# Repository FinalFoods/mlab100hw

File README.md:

# mlab100hw
Hardware Microbiota Personal Lab 100

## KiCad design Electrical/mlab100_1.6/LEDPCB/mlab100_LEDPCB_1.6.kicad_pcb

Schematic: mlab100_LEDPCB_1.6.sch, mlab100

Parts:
J14, J15, J16: Conn_01x06_Male; Pin_Header_Angled_2x03_Pitch1.27mm

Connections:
/LEDBoard1/3V3: J14.5; also elsewhere on the board
/LEDBoard1/12V: J14.6; also elsewhere on the board
/LEDBoard1/GND: J14.1, J14.2; also elsewhere on the board
/LEDBoard1/LED: J14.4; also elsewhere on the board
/LEDBoard1/Temp1w: J14.3; also elsewhere on the board
/LEDBoard2/3V3: J15.5; also elsewhere on the board
/LEDBoard2/12V: J15.6; also elsewhere on the board
/LEDBoard2/GND: J15.1, J15.2; also elsewhere on the board
/LEDBoard2/LED: J15.4; also elsewhere on the board
/LEDBoard2/Temp1w: J15.3; also elsewhere on the board
/LEDBoard3/3V3: J16.5; also elsewhere on the board
/LEDBoard3/12V: J16.6; also elsewhere on the board
/LEDBoard3/GND: J16.1, J16.2; also elsewhere on the board
/LEDBoard3/LED: J16.4; also elsewhere on the board
/LEDBoard3/Temp1w: J16.3; also elsewhere on the board

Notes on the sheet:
LED_Temp_Panel

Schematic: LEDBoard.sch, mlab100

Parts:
D1, D2, D4: 470nm; LED_D5.0mm
D3, D6, D7: 470nm; LED_0603
R1: 120; R_1210_HandSoldering
R4: 10k; R_0603
R5: 1k3; R_0603
R6: 8k8; R_0603
U4: DS18B20; TO-92_Molded_Narrow

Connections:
/LEDBoard1/3V3: D6.2, U4.3 (VDD); also elsewhere on the board
/LEDBoard1/12V: D1.2, D3.2, D7.2; also elsewhere on the board
/LEDBoard1/GND: R4.2, R5.2, U4.1 (GND); also elsewhere on the board
/LEDBoard1/LED: R1.2, R6.2; also elsewhere on the board
/LEDBoard1/Temp1w: U4.2 (DQ); also elsewhere on the board
unnamed: D1.1, D2.2
unnamed: D2.1, D4.2
unnamed: D3.1, R4.1
unnamed: D4.1, R1.1
unnamed: D6.1, R5.1
unnamed: D7.1, R6.1

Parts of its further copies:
D5, D8, D9, D10, D11, D12: 470nm; LED_D5.0mm
D13, D14, D15, D16, D17, D18: 470nm; LED_0603
R2, R3: 120; R_1210_HandSoldering
R7, R10: 10k; R_0603
R8, R11: 1k3; R_0603
R9, R12: 8k8; R_0603
U5, U6: DS18B20; TO-92_Molded_Narrow

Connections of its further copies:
/LEDBoard2/3V3: D14.2, U5.3 (VDD); also elsewhere on the board
/LEDBoard2/12V: D5.2, D13.2, D15.2; also elsewhere on the board
/LEDBoard2/GND: R7.2, R8.2, U5.1 (GND); also elsewhere on the board
/LEDBoard2/LED: R2.2, R9.2; also elsewhere on the board
/LEDBoard2/Temp1w: U5.2 (DQ); also elsewhere on the board
/LEDBoard3/3V3: D17.2, U6.3 (VDD); also elsewhere on the board
/LEDBoard3/12V: D10.2, D16.2, D18.2; also elsewhere on the board
/LEDBoard3/GND: R10.2, R11.2, U6.1 (GND); also elsewhere on the board
/LEDBoard3/LED: R3.2, R12.2; also elsewhere on the board
/LEDBoard3/Temp1w: U6.2 (DQ); also elsewhere on the board
unnamed: D5.1, D8.2
unnamed: D8.1, D9.2
unnamed: D9.1, R2.1
unnamed: D10.1, D11.2
unnamed: D11.1, D12.2
unnamed: D12.1, R3.1
unnamed: D13.1, R7.1
unnamed: D14.1, R8.1
unnamed: D15.1, R9.1
unnamed: D16.1, R10.1
unnamed: D17.1, R11.1
unnamed: D18.1, R12.1

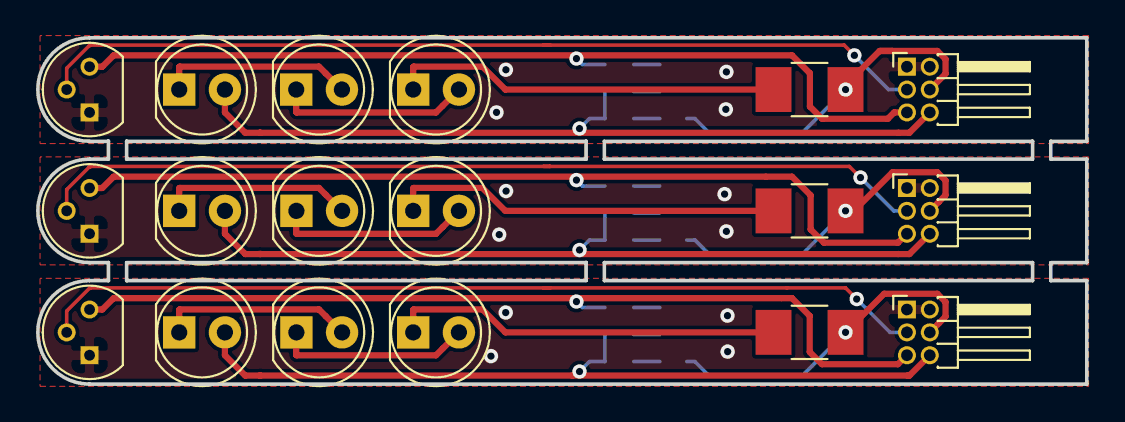
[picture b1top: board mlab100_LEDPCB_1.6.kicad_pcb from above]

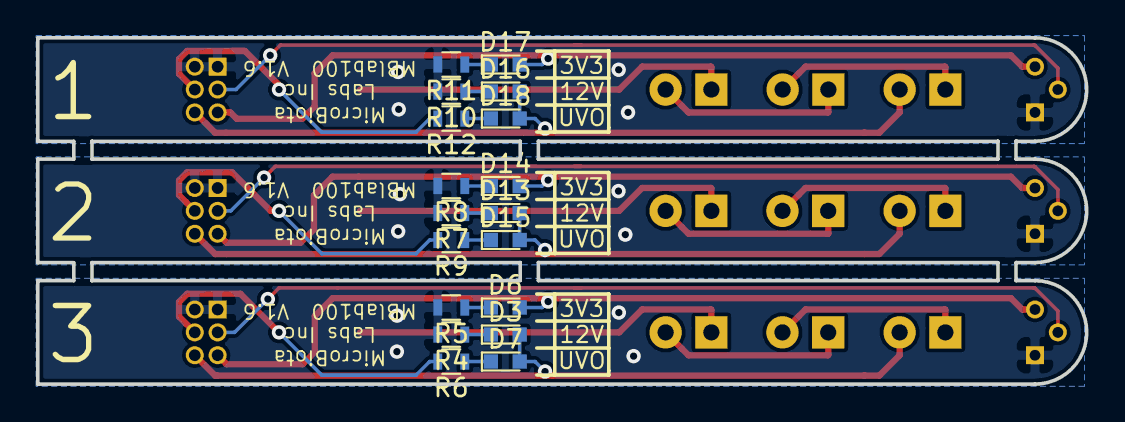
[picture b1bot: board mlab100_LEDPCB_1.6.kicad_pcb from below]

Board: 2 copper layers, 58.3 x 19.2 mm, 36 parts (18 on the bottom side), 33 nets.

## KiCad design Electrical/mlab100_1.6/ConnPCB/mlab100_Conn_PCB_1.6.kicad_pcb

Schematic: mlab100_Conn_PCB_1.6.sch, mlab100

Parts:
J3: Conn_01x12_Male; Pin_Header_Straight_2x06_Pitch2.54mm_SMD
J8, J9, J10: Conn_01x06_Male; Pin_Header_Straight_2x03_Pitch1.27mm
J11, J12, J13: Conn_01x02_Male; Pin_Header_Straight_1x02_Pitch2.54mm
MH8, MH9, MH10: MountingHole; MountingHole_3.7mm_Pad

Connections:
3V3_O: J3.3, J8.2, J9.2, J10.2; also elsewhere on the board
12V_O: J3.1, J8.1, J9.1, J10.1, J11.2, J12.2, J13.2; also elsewhere on the board
/AnalogConnPCB/3V3ACtrl: J3.5; also elsewhere on the board
/AnalogConnPCB/5V: J3.11; also elsewhere on the board
/AnalogConnPCB/470nmCtrl: J3.2; also elsewhere on the board
/AnalogConnPCB/HeaterCtrl: J3.12; also elsewhere on the board
/AnalogConnPCB/SPI_CS_ADC: J3.9; also elsewhere on the board
/AnalogConnPCB/SPI_MISO: J3.8; also elsewhere on the board
/AnalogConnPCB/SPI_MOSI: J3.7; also elsewhere on the board
/AnalogConnPCB/SPI_SCL: J3.6; also elsewhere on the board
GND_O: J3.10, J8.5, J8.6, J9.5, J9.6, J10.5, J10.6; also elsewhere on the board
Heater-: J11.1, J12.1, J13.1; also elsewhere on the board
LED470nm: J8.3, J9.3, J10.3; also elsewhere on the board
Temp1wDaisy: J3.4, J8.4, J9.4, J10.4; also elsewhere on the board

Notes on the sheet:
Conn_Panel

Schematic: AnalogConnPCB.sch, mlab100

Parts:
C1, C2: 1uF; C_0603
C5: 0.1uF; C_0603
D1, D2, D3, D4: LED; LED_0603
D13, D14: D_Photo; LED_D5.0mm
IC1, IC2: ZXGD3006E6QTA; SOT-23-6; Manufacturer_Part_Number ZXGD3006E6QTA; Mouser Part Number 621-ZXGD3006E6QTA
IC3: TCR2EF33,LM(CT; SOT-25; Manufacturer_Part_Number TCR2EF33,LM(CT; DigiKey Part Number TCR2EF33LM(CTDKR-ND
IC4: ADC122S021CIMM_NOPB; SOP65P490X110-8N; Manufacturer_Part_Number ADC122S021CIMM/NOPB
JP1: Jumper; R_0603
Q1, Q3: AOD4184A; TO-252-2
R1, R4: 1k3; R_0603
R2: 3k; R_0603
R3, R15, R16: 10k; R_0603
R12, R13: 3k3; R_0603
R14: 4k7; R_0603

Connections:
3V3_O: D2.2, R14.2; also elsewhere on the board
12V_O: D4.2, IC1.1, IC2.1; also elsewhere on the board
+3.3VA: C2.1, C5.1, D1.2, IC3.5, IC4.2; also elsewhere on the board
/AnalogConnPCB/3V3ACtrl: IC3.3; also elsewhere on the board
/AnalogConnPCB/5V: C1.1, D3.2, IC3.1; also elsewhere on the board
/AnalogConnPCB/470nmCtrl: R13.1; also elsewhere on the board
/AnalogConnPCB/HeaterCtrl: R12.1; also elsewhere on the board
/AnalogConnPCB/SPI_CS_ADC: IC4.1; also elsewhere on the board
/AnalogConnPCB/SPI_MISO: IC4.7; also elsewhere on the board
/AnalogConnPCB/SPI_MOSI: IC4.6; also elsewhere on the board
/AnalogConnPCB/SPI_SCL: IC4.8; also elsewhere on the board
/AnalogConnPCB/sheet5C67EBE6/A+: D13.1; also elsewhere on the board
/AnalogConnPCB/sheet5C67EBE6/Aout: IC4.5; also elsewhere on the board
/AnalogConnPCB/sheet5C67EBE6/B+: D14.1; also elsewhere on the board
/AnalogConnPCB/sheet5C67EBE6/Bout: IC4.4; also elsewhere on the board
GNDA: C1.2, C2.2, C5.2, D13.2, D14.2, IC3.2, IC4.3, JP1.2, R1.2; also elsewhere on the board
GND_O: IC1.3, IC2.3, JP1.1, Q1.3, Q3.3, R2.2, R3.2, R4.2, R15.2, R16.2; also elsewhere on the board
Heater-: Q1.2; also elsewhere on the board
LED470nm: Q3.2; also elsewhere on the board
unnamed: D1.1, R1.1
unnamed: D2.1, R4.1
unnamed: D3.1, R2.1
unnamed: D4.1, R3.1
unnamed: IC1.2, R12.2
unnamed: IC1.4, IC1.6, Q1.1, R15.1
unnamed: IC2.2, R13.2
unnamed: IC2.4, IC2.6, Q3.1, R16.1
Temp1wDaisy: R14.1; also elsewhere on the board

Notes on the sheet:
Analog
Dual Op Amp
ADC

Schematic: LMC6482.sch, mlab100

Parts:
C9, C10: 100pF; C_0603
R10, R11: 1M; R_0603
RV1: 5M; Potentiometer_Trimmer_Bourns_3296W
RV2: 1M; Potentiometer_Trimmer_Bourns_3296W
U3: LMC6482; SOIC-8-N

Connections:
+3.3VA: U3.8 (V+); also elsewhere on the board
/AnalogConnPCB/sheet5C67EBE6/A+: C9.2, R10.2, U3.2 (-); also elsewhere on the board
/AnalogConnPCB/sheet5C67EBE6/Aout: C9.1, RV1.1, U3.1; also elsewhere on the board
/AnalogConnPCB/sheet5C67EBE6/B+: C10.2, R11.2, U3.6 (-); also elsewhere on the board
/AnalogConnPCB/sheet5C67EBE6/Bout: C10.1, RV2.1, U3.7; also elsewhere on the board
GNDA: U3.3 (+), U3.4 (V-), U3.5 (+); also elsewhere on the board
unnamed: R10.1, RV1.2, RV1.3
unnamed: R11.1, RV2.2, RV2.3

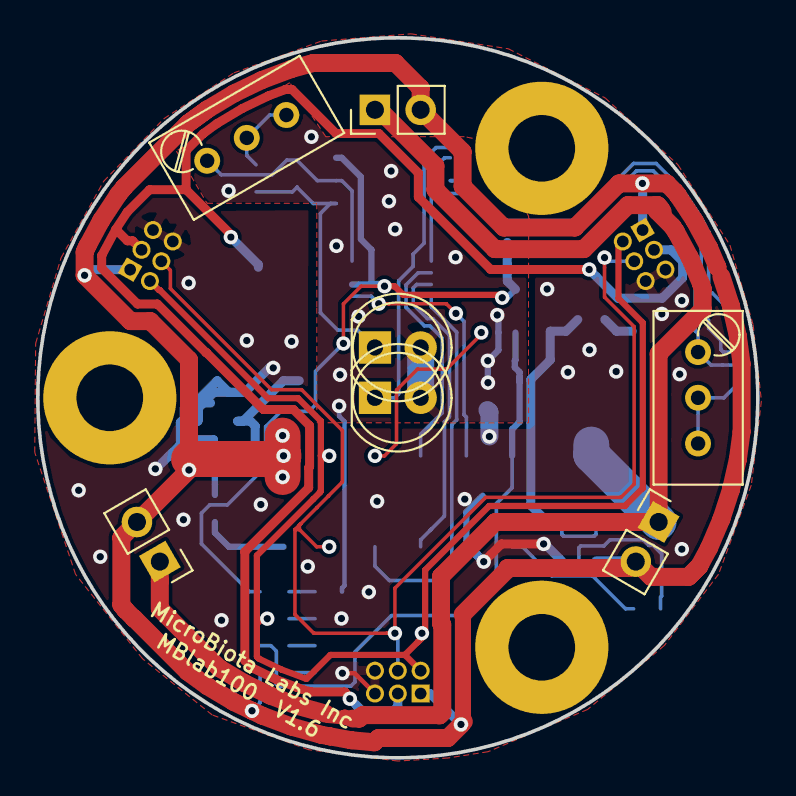
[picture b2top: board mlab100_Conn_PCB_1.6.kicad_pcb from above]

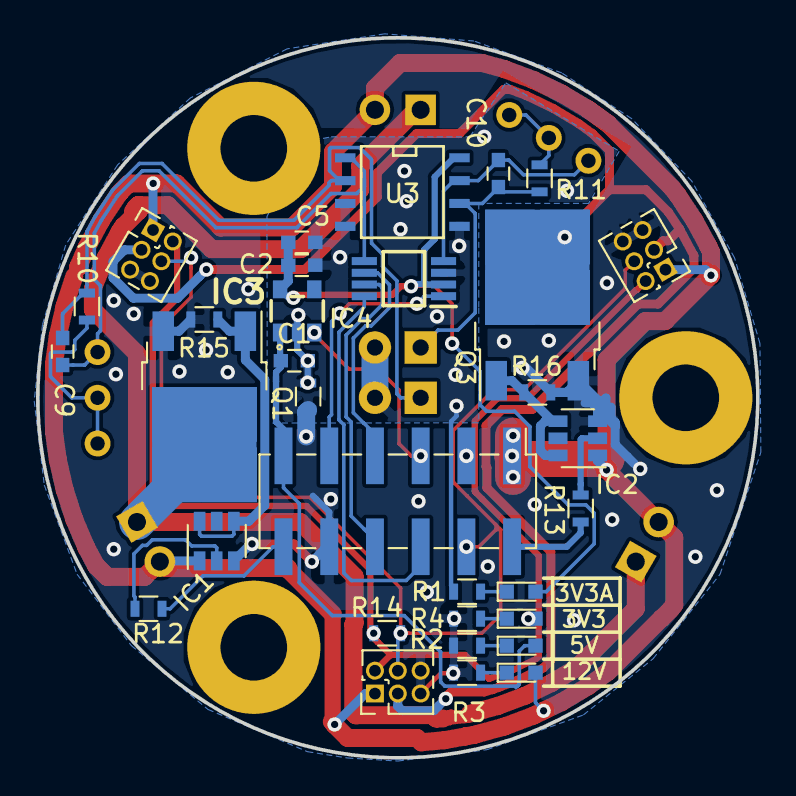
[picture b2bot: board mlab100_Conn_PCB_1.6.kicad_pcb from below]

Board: 2 copper layers, 40.0 x 40.0 mm, 42 parts (32 on the bottom side), 30 nets.

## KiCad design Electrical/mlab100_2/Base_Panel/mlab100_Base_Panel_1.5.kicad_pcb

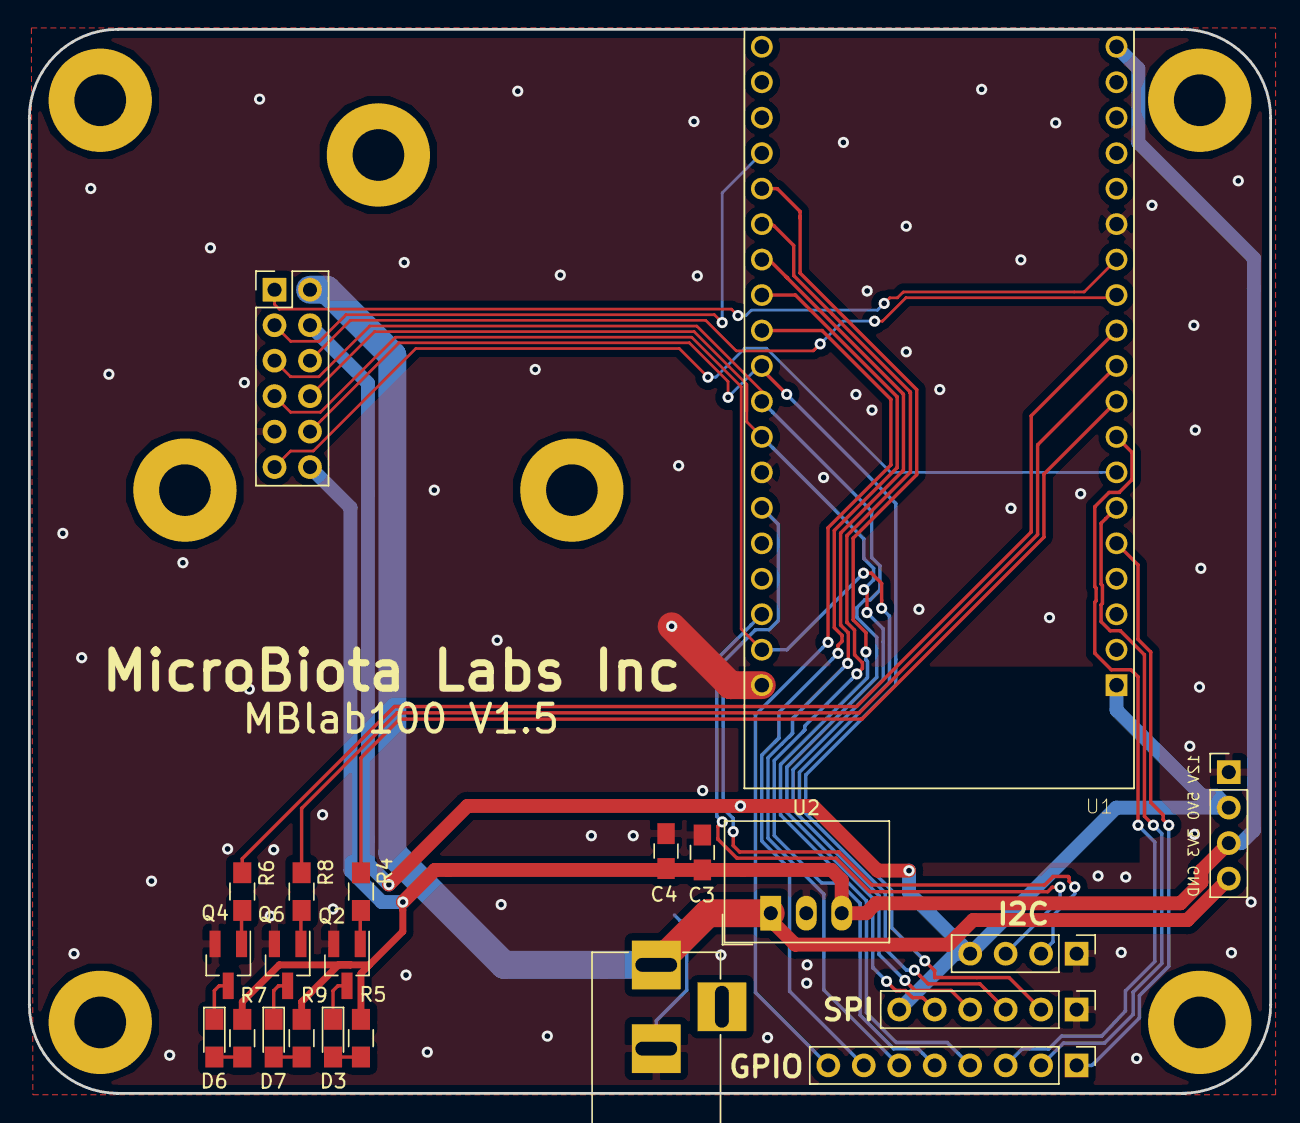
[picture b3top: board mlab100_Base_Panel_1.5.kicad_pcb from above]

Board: 2 copper layers, 88.9 x 76.2 mm, 29 parts (0 on the bottom side), 34 nets.

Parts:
C3: 10uF; C_0805_HandSoldering
C4: 1uF; C_0805_HandSoldering
D3: green; LED_0805_HandSoldering
D6: red; LED_0805_HandSoldering
D7: yellow; LED_0805_HandSoldering
J1: Conn_01x04; Pin_Header_Straight_1x04_Pitch2.54mm
J2: Conn_01x12_Female; Pin_Header_Straight_2x06_Pitch2.54mm
J4: Conn_01x02_Male; BARREL_JACK
J5: Conn_01x08_Male; Pin_Header_Straight_1x08_Pitch2.54mm
J6: Conn_01x06_Male; Pin_Header_Straight_1x06_Pitch2.54mm
J7: Conn_01x04_Male; Pin_Header_Straight_1x04_Pitch2.54mm
MH1, MH2, MH3, MH4, MH5, MH6, MH7: MountingHole; MountingHole_3.7mm_Pad
Q2, Q4, Q6: DMN3404; SOT-23_Handsoldering
R4, R6, R8: 3k3; R_0805_HandSoldering
R5, R7, R9: 1k; R_0805_HandSoldering
U1: ESP32-DEVKITC-32D; MODULE_ESP32-DEVKITC-32D
U2: R-78E5.0-1.0; DCDC-Conv_RECOM_R-78E-0.5

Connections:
+3V3: J1.2, J2.4, J6.6, J7.4, U1.1
+5V: C3.1, C4.1, J1.3, J2.12, R5.2, R7.2, R9.2, U1.19, U2.3
+12V: J1.4, J2.2, J4.1, U2.1
CTRL_3V3A: J2.6, U1.12
CTRL_470nm: J2.1, U1.13
CTRL_Heater: J2.11, U1.7
GND: C3.2, C4.2, J1.1, J2.9, J4.2, J6.1, J7.1, Q2.2, Q4.2, Q6.2, U1.14, U1.20, U1.26, U2.2
I2C_SCL: J7.3, U1.22
I2C_SDA: J7.2, U1.25
I34: J5.1, U1.5
I35: J5.2, U1.6
IO0: J5.5, U1.33
IO2: J5.4, U1.34
IO4: J5.6, U1.32
IO16: J5.7, U1.31
IO17: J5.8, U1.30
IO33: J5.3, U1.8
LED_G: R4.1, U1.9
LED_R: R6.1, U1.11
LED_Y: R8.1, U1.10
unnamed: D3.1, Q2.3
unnamed: D3.2, R5.1
unnamed: D6.1, Q4.3
unnamed: D6.2, R7.1
unnamed: D7.1, Q6.3
unnamed: D7.2, R9.1
unnamed: Q2.1, R4.2
unnamed: Q4.1, R6.2
unnamed: Q6.1, R8.2
SPI_CS_ADC: J2.10, J6.2, U1.29
SPI_MISO: J2.7, J6.3, U1.21
SPI_MOSI: J2.8, J6.4, U1.27
SPI_SCL: J2.5, J6.5, U1.28
TEMP1W: J2.3, U1.35

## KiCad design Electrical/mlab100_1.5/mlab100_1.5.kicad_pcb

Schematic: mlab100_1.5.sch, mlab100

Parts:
C3: 10uF; C_0805_HandSoldering
C4: 1uF; C_0805_HandSoldering
D3: green; LED_0805_HandSoldering
D6: red; LED_0805_HandSoldering
D7: yellow; LED_0805_HandSoldering
J1: Conn_01x04; Pin_Header_Straight_1x04_Pitch2.54mm
J2: Conn_01x12_Female; Pin_Header_Straight_2x06_Pitch2.54mm
J3: Conn_01x12_Male; Pin_Header_Straight_2x06_Pitch2.54mm_SMD
J4: Conn_01x02_Male; BARREL_JACK
J5: Conn_01x08_Male; Pin_Header_Straight_1x08_Pitch2.54mm
J6: Conn_01x06_Male; Pin_Header_Straight_1x06_Pitch2.54mm
J7: Conn_01x04_Male; Pin_Header_Straight_1x04_Pitch2.54mm
J8, J9, J10: Conn_01x06_Male; Pin_Header_Straight_2x03_Pitch1.27mm
J11, J12, J13: Conn_01x02_Male; Pin_Header_Straight_1x02_Pitch2.54mm
J14, J15, J16: Conn_01x06_Male; Pin_Header_Angled_2x03_Pitch1.27mm
MH1, MH2, MH3, MH4, MH5, MH6, MH7, MH8, MH9, MH10: MountingHole; MountingHole_3.7mm_Pad
Q2, Q4, Q6: DMN3404; SOT-23_Handsoldering
R4, R6, R8: 3k3; R_0805_HandSoldering
R5, R7, R9: 1k; R_0805_HandSoldering
U1: ESP32-DEVKITC-32D; MODULE_ESP32-DEVKITC-32D
U2: R-78E5.0-1.0; DCDC-Conv_RECOM_R-78E-0.5

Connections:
3V3_O: J3.3, J8.2, J9.2, J10.2; also elsewhere on the board
12V_O: J3.1, J8.1, J9.1, J10.1, J11.2, J12.2, J13.2; also elsewhere on the board
+3V3: J1.2, J2.4, J6.6, J7.4, U1.1
+5V: C3.1, C4.1, J1.3, J2.12, R5.2, R7.2, R9.2, U1.19, U2.3 (OUT)
+12V: J1.4, J2.2, J4.1, U2.1 (IN)
/AnalogConnPCB/3V3ACtrl: J3.5; also elsewhere on the board
/AnalogConnPCB/5V: J3.11; also elsewhere on the board
/AnalogConnPCB/470nmCtrl: J3.2; also elsewhere on the board
/AnalogConnPCB/HeaterCtrl: J3.12; also elsewhere on the board
/AnalogConnPCB/SPI_CS_ADC: J3.9; also elsewhere on the board
/AnalogConnPCB/SPI_MISO: J3.8; also elsewhere on the board
/AnalogConnPCB/SPI_MOSI: J3.7; also elsewhere on the board
/AnalogConnPCB/SPI_SCL: J3.6; also elsewhere on the board
/LEDBoard1/3V3: J14.5; also elsewhere on the board
/LEDBoard1/12V: J14.6; also elsewhere on the board
/LEDBoard1/GND: J14.1, J14.2; also elsewhere on the board
/LEDBoard1/LED: J14.4; also elsewhere on the board
/LEDBoard1/Temp1w: J14.3; also elsewhere on the board
/LEDBoard2/3V3: J15.5; also elsewhere on the board
/LEDBoard2/12V: J15.6; also elsewhere on the board
/LEDBoard2/GND: J15.1, J15.2; also elsewhere on the board
/LEDBoard2/LED: J15.4; also elsewhere on the board
/LEDBoard2/Temp1w: J15.3; also elsewhere on the board
/LEDBoard3/3V3: J16.5; also elsewhere on the board
/LEDBoard3/12V: J16.6; also elsewhere on the board
/LEDBoard3/GND: J16.1, J16.2; also elsewhere on the board
/LEDBoard3/LED: J16.4; also elsewhere on the board
/LEDBoard3/Temp1w: J16.3; also elsewhere on the board
CTRL_3V3A: J2.6, U1.12
CTRL_470nm: J2.1, U1.13
CTRL_Heater: J2.11, U1.7
GND: C3.2, C4.2, J1.1, J2.9, J4.2, J6.1, J7.1, Q2.2, Q4.2, Q6.2, U1.14, U1.20, U1.26, U2.2 (GND)
GND_O: J3.10, J8.5, J8.6, J9.5, J9.6, J10.5, J10.6; also elsewhere on the board
Heater-: J11.1, J12.1, J13.1; also elsewhere on the board
I2C_SCL: J7.3, U1.22
I2C_SDA: J7.2, U1.25
I34: J5.1, U1.5
I35: J5.2, U1.6
IO0: J5.5, U1.33
IO2: J5.4, U1.34
IO4: J5.6, U1.32
IO16: J5.7, U1.31
IO17: J5.8, U1.30
IO33: J5.3, U1.8
LED470nm: J8.3, J9.3, J10.3; also elsewhere on the board
LED_G: R4.1, U1.9
LED_R: R6.1, U1.11
LED_Y: R8.1, U1.10
unnamed: D3.1, Q2.3
unnamed: D3.2, R5.1
unnamed: D6.1, Q4.3
unnamed: D6.2, R7.1
unnamed: D7.1, Q6.3
unnamed: D7.2, R9.1
unnamed: Q2.1, R4.2
unnamed: Q4.1, R6.2
unnamed: Q6.1, R8.2
SPI_CS_ADC: J2.10, J6.2, U1.29
SPI_MISO: J2.7, J6.3, U1.21
SPI_MOSI: J2.8, J6.4, U1.27
SPI_SCL: J2.5, J6.5, U1.28
TEMP1W: J2.3, U1.35
Temp1wDaisy: J3.4, J8.4, J9.4, J10.4; also elsewhere on the board

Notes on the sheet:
LED_Temp_Panel
Analog_Conn_Panel
Input_Output
ESP32
Indication LEDs
Mounting Points
Power
Base_Panel

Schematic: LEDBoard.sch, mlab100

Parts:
D1, D2, D4: 470nm; LED_D5.0mm
R1: 120; R_1210_HandSoldering
U4: DS18B20; TO-92_Molded_Narrow

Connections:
/LEDBoard1/3V3: U4.3 (VDD); also elsewhere on the board
/LEDBoard1/12V: D1.2; also elsewhere on the board
/LEDBoard1/GND: U4.1 (GND); also elsewhere on the board
/LEDBoard1/LED: R1.2; also elsewhere on the board
/LEDBoard1/Temp1w: U4.2 (DQ); also elsewhere on the board
unnamed: D1.1, D2.2
unnamed: D2.1, D4.2
unnamed: D4.1, R1.1

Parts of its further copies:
D5, D8, D9, D10, D11, D12: 470nm; LED_D5.0mm
R2, R3: 120; R_1210_HandSoldering
U5, U6: DS18B20; TO-92_Molded_Narrow

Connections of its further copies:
/LEDBoard2/3V3: U5.3 (VDD); also elsewhere on the board
/LEDBoard2/12V: D5.2; also elsewhere on the board
/LEDBoard2/GND: U5.1 (GND); also elsewhere on the board
/LEDBoard2/LED: R2.2; also elsewhere on the board
/LEDBoard2/Temp1w: U5.2 (DQ); also elsewhere on the board
/LEDBoard3/3V3: U6.3 (VDD); also elsewhere on the board
/LEDBoard3/12V: D10.2; also elsewhere on the board
/LEDBoard3/GND: U6.1 (GND); also elsewhere on the board
/LEDBoard3/LED: R3.2; also elsewhere on the board
/LEDBoard3/Temp1w: U6.2 (DQ); also elsewhere on the board
unnamed: D5.1, D8.2
unnamed: D8.1, D9.2
unnamed: D9.1, R2.1
unnamed: D10.1, D11.2
unnamed: D11.1, D12.2
unnamed: D12.1, R3.1

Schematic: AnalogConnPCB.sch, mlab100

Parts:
C1, C2: 1uF; C_0603
C5: 0.1uF; C_0603
D13, D14: D_Photo; LED_D5.0mm
IC1, IC2: ZXGD3006E6QTA; SOT-23-6; Manufacturer_Part_Number ZXGD3006E6QTA; Mouser Part Number 621-ZXGD3006E6QTA
IC3: TCR2EF33,LM(CT; SOT-25; Manufacturer_Part_Number TCR2EF33,LM(CT; DigiKey Part Number TCR2EF33LM(CTDKR-ND
IC4: ADC122S021CIMM_NOPB; SOP65P490X110-8N; Manufacturer_Part_Number ADC122S021CIMM/NOPB
JP1: Jumper; R_0603
Q1, Q3: AOD4184A; TO-252-2
R12, R13: 3k3; R_0603
R14: 4k7; R_0603
R15, R16: 10k; R_0603

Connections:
3V3_O: R14.2; also elsewhere on the board
12V_O: IC1.1, IC2.1; also elsewhere on the board
+3.3VA: C2.1, C5.1, IC3.5, IC4.2; also elsewhere on the board
/AnalogConnPCB/3V3ACtrl: IC3.3; also elsewhere on the board
/AnalogConnPCB/5V: C1.1, IC3.1; also elsewhere on the board
/AnalogConnPCB/470nmCtrl: R13.1; also elsewhere on the board
/AnalogConnPCB/HeaterCtrl: R12.1; also elsewhere on the board
/AnalogConnPCB/SPI_CS_ADC: IC4.1; also elsewhere on the board
/AnalogConnPCB/SPI_MISO: IC4.7; also elsewhere on the board
/AnalogConnPCB/SPI_MOSI: IC4.6; also elsewhere on the board
/AnalogConnPCB/SPI_SCL: IC4.8; also elsewhere on the board
/AnalogConnPCB/sheet5C67EBE6/A+: D13.1; also elsewhere on the board
/AnalogConnPCB/sheet5C67EBE6/Aout: IC4.5; also elsewhere on the board
/AnalogConnPCB/sheet5C67EBE6/B+: D14.1; also elsewhere on the board
/AnalogConnPCB/sheet5C67EBE6/Bout: IC4.4; also elsewhere on the board
GNDA: C1.2, C2.2, C5.2, D13.2, D14.2, IC3.2, IC4.3, JP1.2; also elsewhere on the board
GND_O: IC1.3, IC2.3, JP1.1, Q1.3, Q3.3, R15.2, R16.2; also elsewhere on the board
Heater-: Q1.2; also elsewhere on the board
LED470nm: Q3.2; also elsewhere on the board
unnamed: IC1.2, R12.2
unnamed: IC1.4, IC1.6, Q1.1, R15.1
unnamed: IC2.2, R13.2
unnamed: IC2.4, IC2.6, Q3.1, R16.1
Temp1wDaisy: R14.1; also elsewhere on the board

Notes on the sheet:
Analog
Dual Op Amp
ADC

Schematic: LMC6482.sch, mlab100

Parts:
C9, C10: 100pF; C_0603
R10, R11: 1M; R_0603
RV1: 5M; Potentiometer_Trimmer_Bourns_3296W
RV2: 1M; Potentiometer_Trimmer_Bourns_3296W
U3: LMC6482; SOIC-8-N

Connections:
+3.3VA: U3.8 (V+); also elsewhere on the board
/AnalogConnPCB/sheet5C67EBE6/A+: C9.2, R10.2, U3.2 (-); also elsewhere on the board
/AnalogConnPCB/sheet5C67EBE6/Aout: C9.1, RV1.1, U3.1; also elsewhere on the board
/AnalogConnPCB/sheet5C67EBE6/B+: C10.2, R11.2, U3.6 (-); also elsewhere on the board
/AnalogConnPCB/sheet5C67EBE6/Bout: C10.1, RV2.1, U3.7; also elsewhere on the board
GNDA: U3.3 (+), U3.4 (V-), U3.5 (+); also elsewhere on the board
unnamed: R10.1, RV1.2, RV1.3
unnamed: R11.1, RV2.2, RV2.3

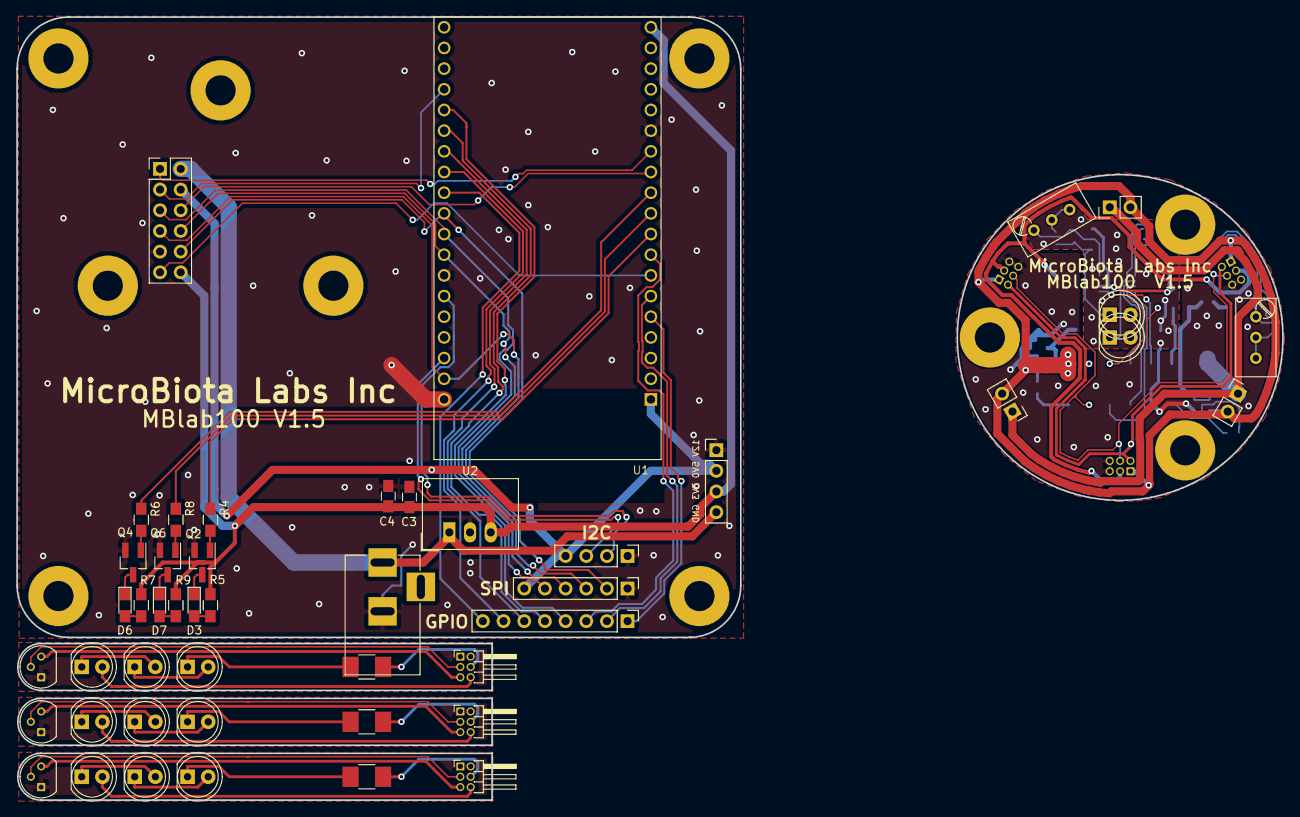
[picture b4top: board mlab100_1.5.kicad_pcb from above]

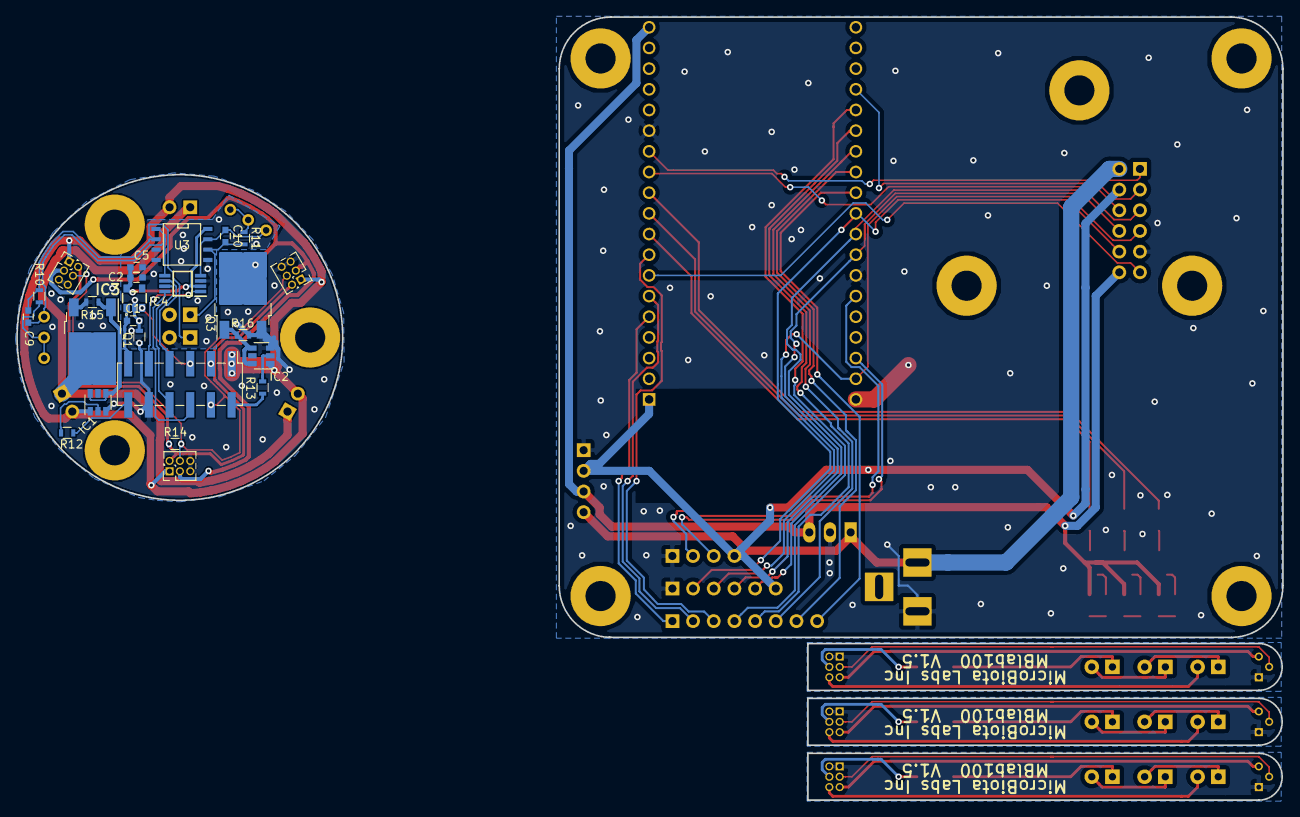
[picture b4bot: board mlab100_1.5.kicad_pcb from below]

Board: 2 copper layers, 155.5 x 96.2 mm, 81 parts (24 on the bottom side), 84 nets.

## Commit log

2018-12-05 initial checkin
2018-12-12 Merging shit
2018-12-13 Schematic PDF Updated
2019-01-03 1.0 finished
2019-01-22 v1.0
2019-01-29 MBlabs100_1.5 sent off for manufacture
2019-02-04 PCB 1.5 done
2019-02-04 mlab100 Gerbers generated and shipped
2019-02-19 v1.6 sent out
